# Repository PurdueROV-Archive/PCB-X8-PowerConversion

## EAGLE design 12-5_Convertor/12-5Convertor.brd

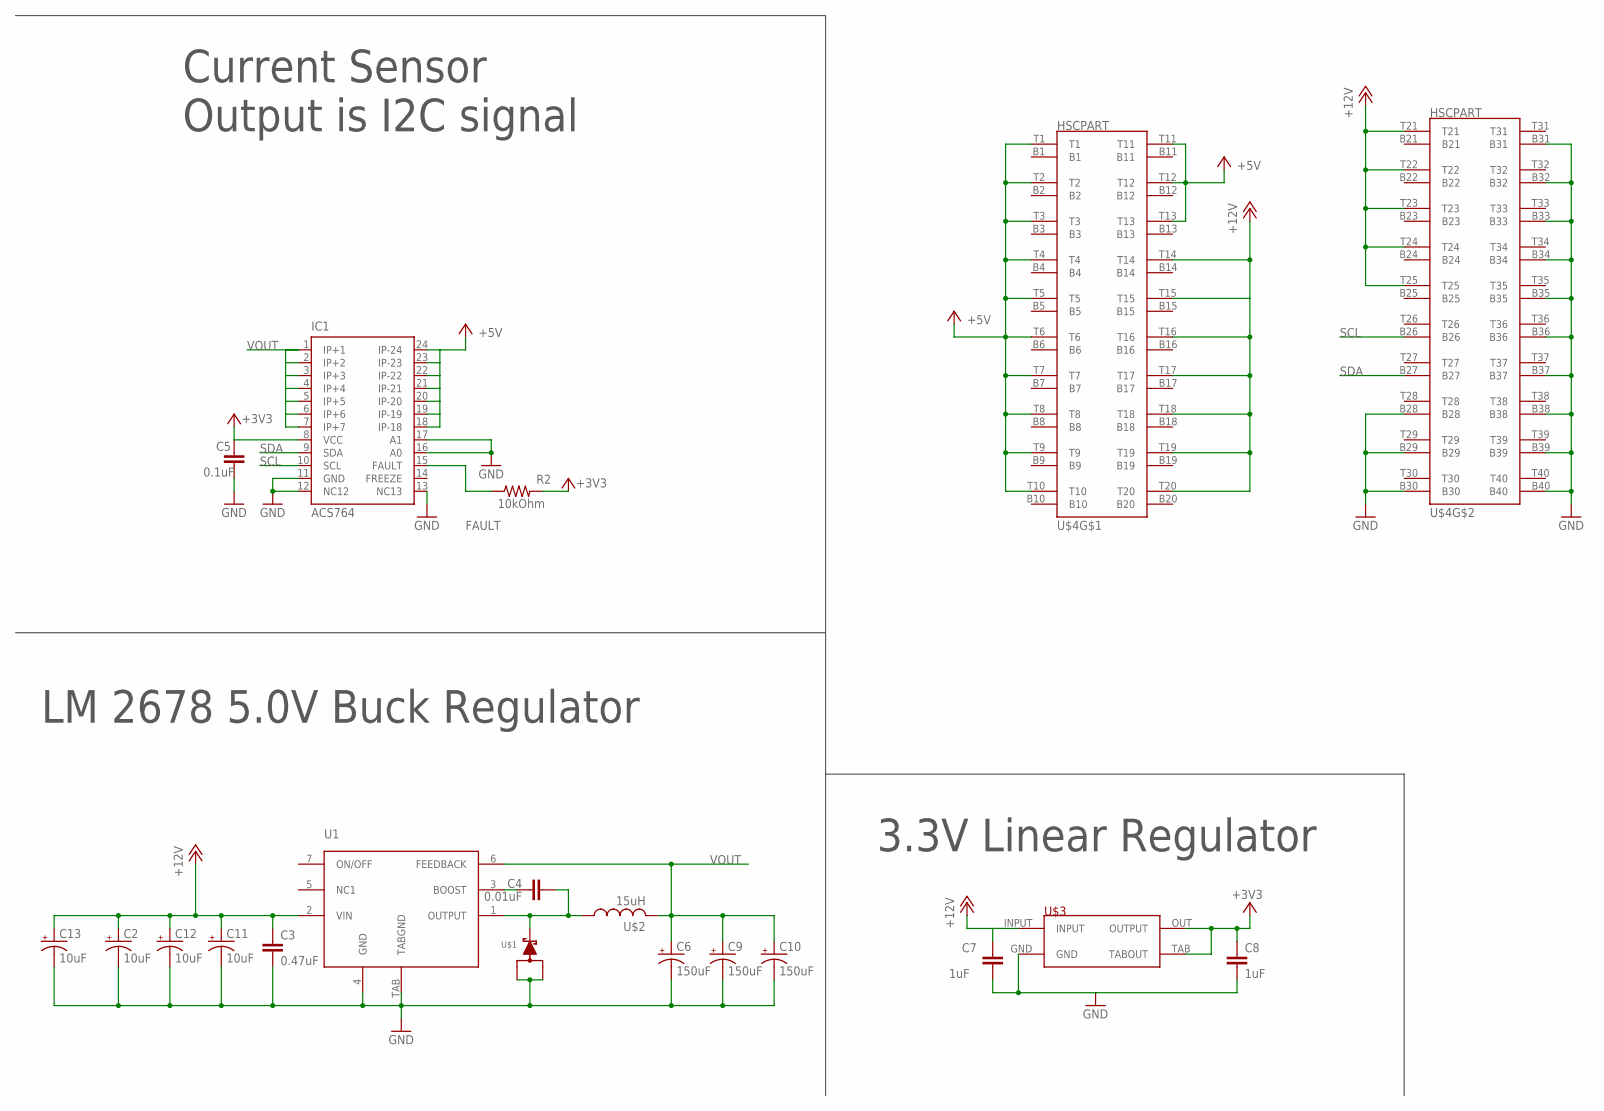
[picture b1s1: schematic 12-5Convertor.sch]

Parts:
C2, C11, C12, C13: 10uF; CTAN(7.30_4.30MM)
C3: 0.47uF; 0805
C4: 0.01uF; 0603-CAP
C5: 0.1uF; C0603
C6, C9, C10: 150uF; CTAN(7.30_4.30MM)
C7, C8: 1uF; 0603-CAP
IC1: ACS764; SSOP24
R2: 10kOhm; R0603
U1: LM2678
U$1: SWITCHMODE_SCHOTTKY; DPAK-3
U$2: 15uH; HCMA1305
U$3: NCP1117
U$4: HSCPART; HSC8-40PINOUUT

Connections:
+3V3: C5.1, C8.1, IC1.8 (VCC), R2.2, U$3.OUT (OUTPUT), U$3.TAB (TABOUT)
+5V: IC1.18 (IP-18), IC1.19 (IP-19), IC1.20 (IP-20), IC1.21 (IP-21), IC1.22 (IP-22), IC1.23 (IP-23), IC1.24 (IP-24), U$4.T1, U$4.T2, U$4.T3, U$4.T4, U$4.T5, U$4.T6, U$4.T7, U$4.T8, U$4.T9, U$4.T10, U$4.T11, U$4.T12, U$4.T13
+12V: C2.+, C3.1, C7.1, C11.+, C12.+, C13.+, U1.2 (VIN), U$3.INPUT, U$4.T14, U$4.T15, U$4.T16, U$4.T17, U$4.T18, U$4.T19, U$4.T20, U$4.T21, U$4.T22, U$4.T23, U$4.T24, U$4.T25
FAULT: IC1.15 (FAULT), R2.1
GND: C2.-, C3.2, C5.2, C6.-, C7.2, C8.2, C9.-, C10.-, C11.-, C12.-, C13.-, IC1.11 (GND), IC1.12 (NC12), IC1.13 (NC13), IC1.16 (A0), IC1.17 (A1), U1.4 (GND), U1.TAB (TABGND), U$1.P$1, U$1.P$3, U$3.GND, U$4.B28, U$4.B29, U$4.B30, U$4.B31, U$4.B32, U$4.B33, U$4.B34, U$4.B35, U$4.B36, U$4.B37, U$4.B38, U$4.B39, U$4.B40
unnamed: C4.1, U1.3 (BOOST)
unnamed: C4.2, U1.1 (OUTPUT), U$1.P$4, U$2.P$1 (1)
SCL: IC1.10 (SCL), U$4.B26
SDA: IC1.9 (SDA), U$4.B27
VOUT: C6.+, C9.+, C10.+, IC1.1 (IP+1), IC1.2 (IP+2), IC1.3 (IP+3), IC1.4 (IP+4), IC1.5 (IP+5), IC1.6 (IP+6), IC1.7 (IP+7), U1.6 (FEEDBACK), U$2.P$2 (2)

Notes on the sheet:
LM 2678 5.0V Buck Regulator
3.3V Linear Regulator
Current Sensor Output is I2C signal

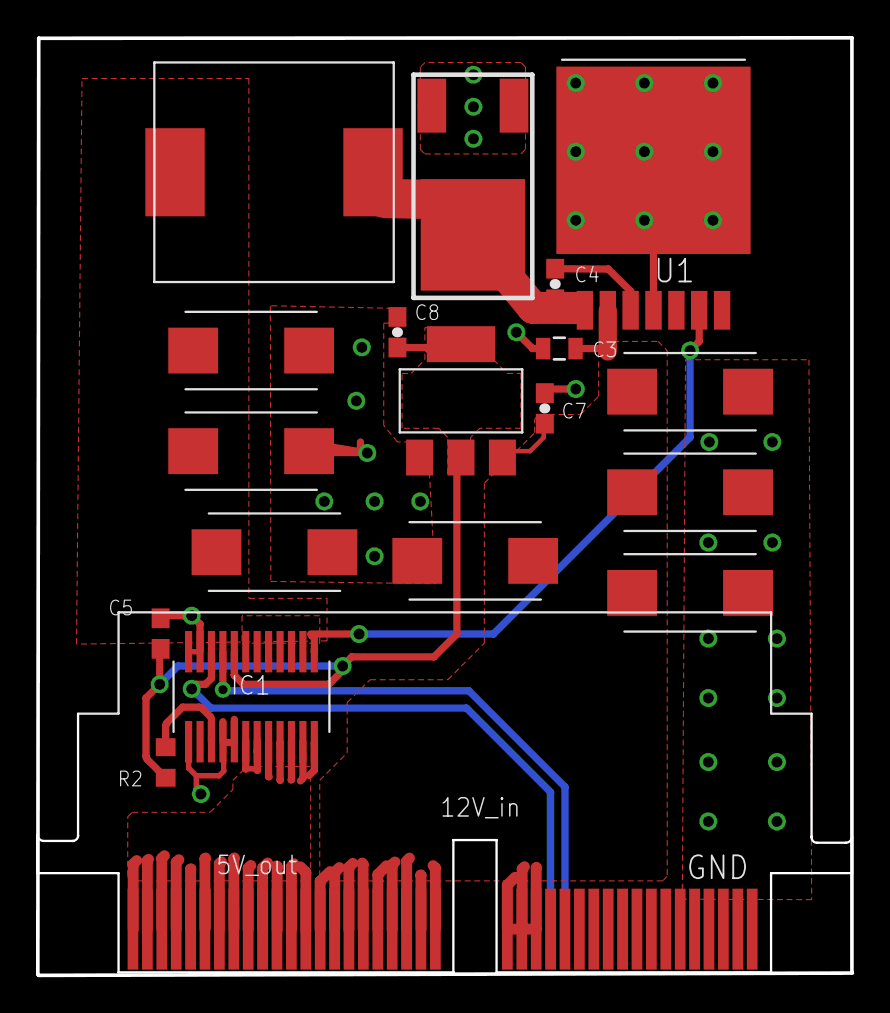
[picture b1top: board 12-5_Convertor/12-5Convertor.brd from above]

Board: 2 copper layers, 45.3 x 52.1 mm, 19 parts (0 on the bottom side), 10 nets.

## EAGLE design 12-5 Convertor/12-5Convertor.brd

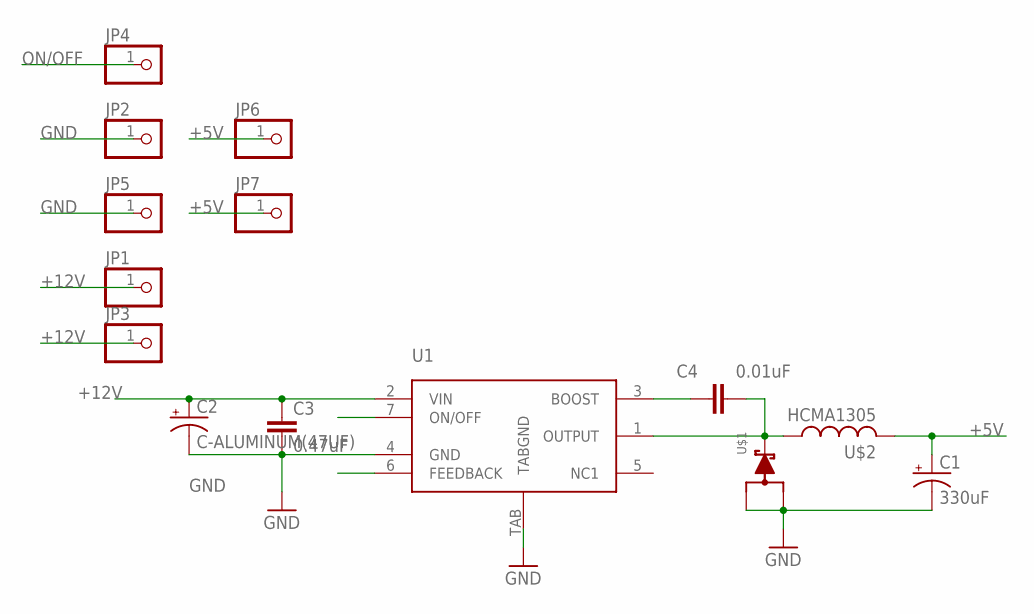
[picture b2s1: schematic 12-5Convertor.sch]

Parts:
C1: 330uF; CPOL-US(10.3_10.3MM)
C2: C-ALUMINUM(47UF); CPOL-US(8.3_8.3MM)
C3: 0.47uF; 0805
C4: 0.01uF; 0603-CAP
JP1, JP2, JP3, JP4, JP5, JP6, JP7: PINHD-1X1; 1X01
U1: LM2678
U$1: SWITCHMODE_SCHOTTKY; DPAK-3
U$2: HCMA1305

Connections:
+5V: C1.+, JP6.1, JP7.1, U1.6 (FEEDBACK), U$2.P$2 (2)
+12V: C2.+, C3.1, JP1.1, JP3.1, U1.2 (VIN)
GND: C1.-, C2.-, C3.2, JP2.1, JP5.1, U1.4 (GND), U1.TAB (TABGND), U$1.P$1, U$1.P$3
unnamed: C4.1, U1.3 (BOOST)
unnamed: C4.2, U1.1 (OUTPUT), U$1.P$4, U$2.P$1 (1)
ON/OFF: JP4.1, U1.7 (ON/OFF)

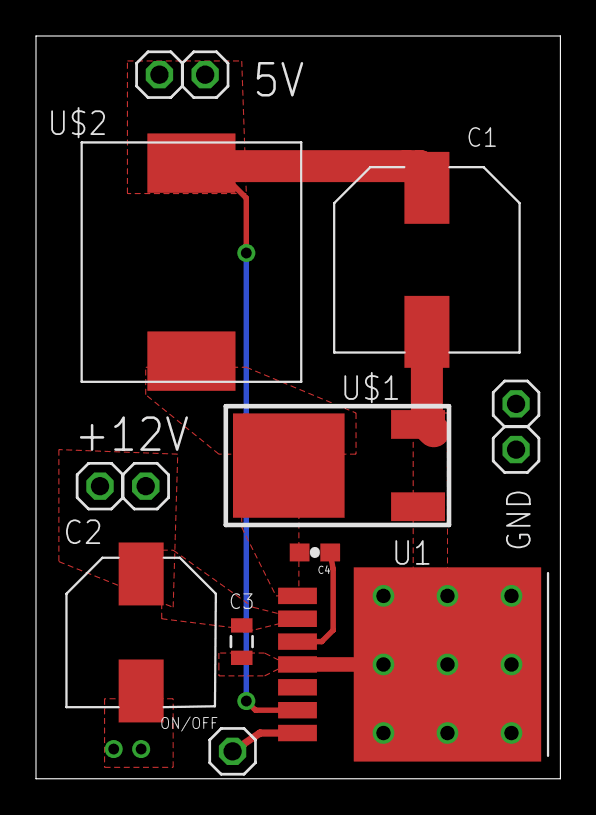
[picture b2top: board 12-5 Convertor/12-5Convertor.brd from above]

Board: 2 copper layers, 29.1 x 41.3 mm, 14 parts (0 on the bottom side), 6 nets.

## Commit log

2015-10-31 A draft of 12-5 Convertor
2015-11-05 adjust the dc-dc 12-5 convertor
2015-11-07 Added Header Pins For testing
2015-11-08 Added labels (still need to verify headers)
2015-11-08 Cleaned the 12-5 buck regulator
2015-11-08 Put finishing touches on buck regulator test board
2015-11-11 Creating a new version of buck regulator
2015-11-11 Fix naming convetion
2015-11-12 Update the buck regulator.
2015-11-13 Sutff for buck regulator
2015-11-14 Fixed labels. Added linear regulator and current sensor
2015-11-17 Cleaned up the buck regulator schematic
2015-11-18 ripped of wires in order to preapare for new board layout
2015-11-22 Updated the power conversion board
2015-12-12 "Added Richard's updated version of the buck converter board"
2015-12-15 Added the board edge connector
2015-12-31 Added tantalum capacitors to buck regulator board
2015-12-31 made the board square and tried to fix the weird polygons
2016-01-05 Edited the silkscreen for the buck regulator board
2016-01-06 Changed the pin order of the backplane connector
2016-01-14 Fixed errors on routing
2016-01-16 cut off copper
2016-01-18 Updated the backplane connector part

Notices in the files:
parts and their libraries:
SparkFun-Passives: Licensing: Creative Commons ShareAlike 4.0 International - https://creativecommons.org/licenses/by-sa/4.0
